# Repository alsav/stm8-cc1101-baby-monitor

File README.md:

STM8-CC1101-BabyMonitor
=======================

Радионяня, радиомаяк на МК STM8S003F3 и микросборке СС1101.
Работает в диапазоне LPD 433Мгц (433300) на 10 канале.

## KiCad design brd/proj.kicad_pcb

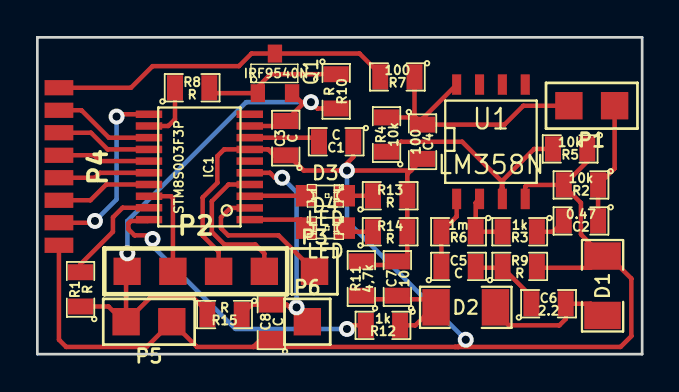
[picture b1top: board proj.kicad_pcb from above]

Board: 2 copper layers, 33.6 x 17.6 mm, 36 parts (0 on the bottom side), 31 nets.

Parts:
C1, C3, C5, C8: C; SM0805
C2: 0.47; SM0805
C4: 100; SM0805
C6: 2.2; SM0805
C7: 10; SM0805
D1, D2: DIODE; SM1206
D3, D4: LED; LED-0805
IC1: STM8S003F3P; tssop-20
P1: CONN_MIC; PIN_ARRAY_2X1
P2: CONN_SWIM; PIN_ARRAY_4x1
P3: CONN_URT; PIN_ARRAY_1
P4: CONN_RF; PIN_ARRAY-8X1-1.25
P5: CONN_PWR; PIN_ARRAY_2X1
P6: CONN_KEY; PIN_ARRAY_1
Q1: IRF9540N; SOT23
R1, R8, R9, R10, R13, R14, R15: R; SM0805
R2, R4, R5: 10k; SM0805
R3, R12: 1k; SM0805
R6: 1m; SM0805
R7: 100; SM0805
R11: 4,7k; SM0805
U1: LM358N; SO8N

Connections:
/CSN: IC1.14, P4.3
/GDO0: IC1.13, P4.2
/GDO1_SO: IC1.17, P4.6
/GDO2: IC1.11, P4.7
/KEY: C8.2, IC1.5, P6.1, R15.1
/LED_PWR: D4.1, IC1.1
/LED_STATE: D3.1, IC1.3
/NRST: IC1.4, P2.4
/PWR_CTL: IC1.12, R8.1
/PWR_SENS: IC1.19, R1.2
/P_VREF: P4.1, Q1.1, R7.2
/SCK: IC1.15, P4.4
/SI: IC1.16, P4.5
/SIG_IN: IC1.20, R12.2
/SWIM: IC1.18, P2.2
/UART_TX: IC1.2, P3.1
GND: C1.1, C3.1, C4.2, C7.2, C8.1, D1.1, IC1.7, P2.3, P4.8, P5.1, R2.2, R5.1, R9.2, R11.2, R13.2, R14.2, U1.4
unnamed: R4.1, R5.2, U1.3
unnamed: C6.2, D1.2, D2.1
unnamed: C5.2, C6.1, R9.1
unnamed: C5.1, R6.2, U1.1
unnamed: R3.2, R6.1, U1.2
unnamed: C2.2, R3.1
unnamed: C7.1, D2.2, R11.1, R12.1
unnamed: C4.1, P1.2, R4.2, R7.1, U1.8
unnamed: C2.1, P1.1, R2.1
unnamed: D3.2, R13.1
unnamed: D4.2, R14.1
unnamed: Q1.2, R8.2, R10.1
unnamed: C1.2, IC1.8
VCC: C3.2, IC1.9, P2.1, P5.2, Q1.3, R1.1, R10.2, R15.2

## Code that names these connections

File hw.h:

/*
Copyright (C) 2015 Alexander Sadakov <al.sadakov_dog_gmail.com>

This program is free software; you can redistribute it and/or
modify it under the terms of the GNU General Public License
as published by the Free Software Foundation; either version 2
of the License, or (at your option) any later version.

This program is distributed in the hope that it will be useful,
but WITHOUT ANY WARRANTY; without even the implied warranty of
MERCHANTABILITY or FITNESS FOR A PARTICULAR PURPOSE.  See the
GNU General Public License for more details.
*/



//
//TST-LED - PUSH-PULL
//
#define TST_LED_PORT GPIOD
#define TST_LED_PIN GPIO_PIN_3
#define TST_LED_ON TST_LED_PORT->ODR |= TST_LED_PIN
#define TST_LED_OFF TST_LED_PORT->ODR &= ~TST_LED_PIN


//
//SWITCH PIN - INPUT || EXTI FALL
//
#define SWITCH_PORT GPIOA
//#define SWITCH_PIN GPIO_PIN_1
#define SWITCH_PIN GPIO_PIN_2
#define SWITCH_EXTI_FALL 0b00000010	//zero-detect-port exti sensitivity (write to CR1)
#define SWITCH_EXTI_RISE 0b00000001

#define ENABLE_SWITCH_EXTI_FALL EXTI->CR1 |= SWITCH_EXTI_FALL
#define DISABLE_SWITCH_EXTI_FALL EXTI->CR1 &= ~SWITCH_EXTI_FALL

#define ENABLE_SWITCH_EXTI_RISE EXTI->CR1 |= SWITCH_EXTI_RISE
#define DISABLE_SWITCH_EXTI_RISE EXTI->CR1 &= ~SWITCH_EXTI_RISE

//
//PWR_CTL
//
#define PWR_CTL_PORT GPIOB
#define PWR_CTL_PIN GPIO_PIN_4
#define PWR_ON PWR_CTL_PORT->ODR &= ~PWR_CTL_PIN
#define PWR_OFF PWR_CTL_PORT->ODR |= PWR_CTL_PIN

//
//LED_PWR && LED_STATE
//
#define LED_PORT GPIOD
#define LED_PWR_PIN GPIO_PIN_4
#define LED_STATE_PIN GPIO_PIN_6

#define LED_PWR_ON LED_PORT->ODR |= LED_PWR_PIN
#define LED_PWR_OFF LED_PORT->ODR &= ~LED_PWR_PIN
#define LED_STATE_ON LED_PORT->ODR |= LED_STATE_PIN
#define LED_STATE_OFF LED_PORT->ODR &= ~LED_STATE_PIN


//
//SIGNAL IN (from mic)
//
//#define SIG_IN_PORT GPIOD
//#define SIG_IN_PIN GPIO_PIN_3
#define SIG_IN_ADC_CHANNEL ADC1_CHANNEL_4


//
//BATTERY MEASURE IN
//
//#define VCC_IN_ADC_CHANNEL ADC1_CHANNEL_3
#define VCC_IN_ADC_CHANNEL ADC1_CHANNEL_12


//
//CC1101
//

//GPIO
#define CC1101_SPI_PORT GPIOC

#define CC1101_CS_PIN GPIO_PIN_4
#define CC1101_SI_PIN GPIO_PIN_6
#define CC1101_SO_PIN GPIO_PIN_7
#define CC1101_SCK_PIN GPIO_PIN_5

#define CC1101_CS_ON CC1101_SPI_PORT->ODR &= ~CC1101_CS_PIN
#define CC1101_CS_OFF CC1101_SPI_PORT->ODR |= CC1101_CS_PIN


#define CC1101_GDO0_PORT GPIOC
#define CC1101_GDO0_PIN GPIO_PIN_3

#define CC1101_GDO2_PORT GPIOB
#define CC1101_GDO2_PIN GPIO_PIN_5

//#define FREQ_CORR 0x26
#define FREQ_CORR 0x1c

#define CC1101_POWER_10DBM 0xc0
#define CC1101_POWER_5DBM 0x84
#define CC1101_POWER_0DBM 0x60
#define CC1101_POWER__10DBM 0x34
#define CC1101_POWER__20DBM 0x0e



//RW Rregisters
#define CC1101_IOCFG2	0x00
#define CC1101_IOCFG1	0x01
#define CC1101_IOCFG0	0x02
#define CC1101_FIFOTHR	0x03
#define CC1101_SYNC1	0x04
#define CC1101_SYNC0	0x05
#define CC1101_PKTLEN	0x06
#define CC1101_PKTCTRL1	0x07
#define CC1101_PKTCTRL0	0x08
#define CC1101_ADDR	0x09
#define CC1101_CHANNR	0x0A
#define CC1101_FSCTRL1	0x0B
#define CC1101_FSCTRL0	0x0C
#define CC1101_FREQ2	0x0D
#define CC1101_FREQ1	0x0E
#define CC1101_FREQ0	0x0F
#define CC1101_MDMCFG4	0x10
#define CC1101_MDMCFG3	0x11
#define CC1101_MDMCFG2	0x12
#define CC1101_MDMCFG1	0x13
#define CC1101_MDMCFG0	0x14
#define CC1101_DEVIATN	0x15
#define CC1101_MCSM2	0x16
#define CC1101_MCSM1	0x17
#define CC1101_MCSM0	0x18
#define CC1101_FOCCFG	0x19
#define CC1101_BSCFG	0x1A
#define CC1101_AGCCTRL2	0x1B
#define CC1101_AGCCTRL1	0x1C
#define CC1101_AGCCTRL0	0x1D
#define CC1101_WOREVT1	0x1E
#define CC1101_WOREVT0	0x1F
#define CC1101_WORCTRL	0x20
#define CC1101_FREND1	0x21
#define CC1101_FREND0	0x22
#define CC1101_FSCAL3	0x23
#define CC1101_FSCAL2	0x24
#define CC1101_FSCAL1	0x25
#define CC1101_FSCAL0	0x26
#define CC1101_RCCTRL1	0x27
#define CC1101_RCCTRL0	0x28
#define CC1101_FSTEST	0x29
#define CC1101_PTEST	0x2A
#define CC1101_AGCTEST	0x2B
#define CC1101_TEST2	0x2C
#define CC1101_TEST1	0x2D
#define CC1101_TEST0	0x2E

#define CC1101_PATABLE	0x3E

//R registers
#define CC1101_PARTNUM	0xB0
#define CC1101_VERSION	0xB1
#define CC1101_FREQEST	0xB2
#define CC1101_LQI	0xB3
#define CC1101_RSSI	0xB4
#define CC1101_MARCSTATE	0xB5
#define CC1101_WORTIME1		0xB6
#define CC1101_WORTIME0		0xB7
#define CC1101_PKTSTATUS	0xB8
#define CC1101_VCO_VC_DAC	0xB9
#define CC1101_TXBYTES		0xBA
#define CC1101_RXBYTES		0xBB
#define CC1101_RCCTRL1_STATUS	0xBC
#define CC1101_RCCTRL0_STATUS	0xBD

//Strobes (RW)
#define CC1101_SRES	0x30
#define CC1101_SFSTXON	0x31
#define CC1101_SXOFF	0x32
#define CC1101_SCAL	0x33
#define CC1101_SRX	0x34
#define CC1101_STX	0x35
#define CC1101_SIDLE	0x36
#define CC1101_SWOR	0x38
#define CC1101_SPWD	0x39
#define CC1101_SFRX	0x3A
#define CC1101_SFTX	0x3B
#define CC1101_SWORRST	0x3C
#define CC1101_SNOP	0x3D


#define CC1101_RXTX_FIFO	0x3F




void HW_Init(void);
void CC1101_Config(void);

uint8_t CC1101_SPITransfer(uint8_t addr, uint8_t data);

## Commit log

2015-06-05 Init!
